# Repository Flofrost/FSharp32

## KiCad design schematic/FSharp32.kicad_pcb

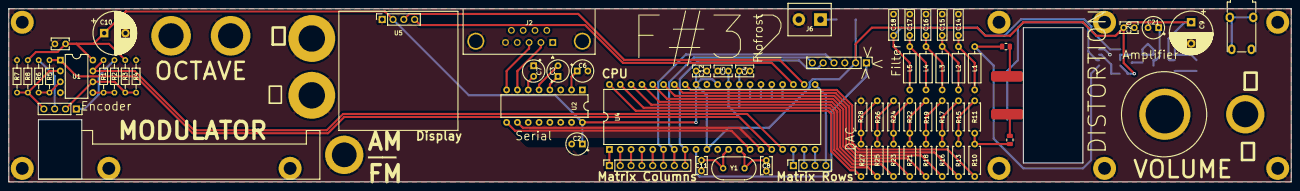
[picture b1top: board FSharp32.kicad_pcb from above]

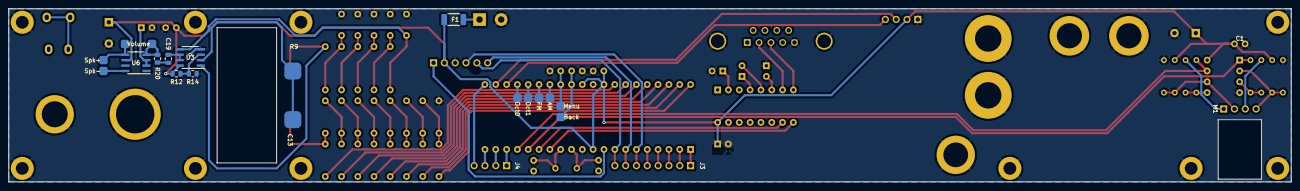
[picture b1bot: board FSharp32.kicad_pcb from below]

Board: 2 copper layers, 301.0 x 40.6 mm, 69 parts (7 on the bottom side), 66 nets.

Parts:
C1, C4, C5, C12, C20: 100n; C_Rect_L4.0mm_W2.5mm_P2.50mm
C2, C3, C6, C7, C21: 10u; CP_Radial_Tantal_D5.0mm_P2.50mm
C8, C11: 18p; C_Rect_L4.0mm_W2.5mm_P2.50mm
C9, C10: 100u; CP_Radial_D10.0mm_P5.00mm
C13, C19: C; C_0805_2012Metric
C14, C15, C16, C17, C18: 94p; C_Rect_L7.0mm_W2.0mm_P5.00mm
F1: Fuse; Fuse_2010_5025Metric
J1: PICkit2; PinHeader_1x06_P2.54mm_Vertical
J2: SerialPort; DSUB-9_Male_Horizontal_P2.77x2.84mm_EdgePinOffset4.94mm_Hou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
J3: MatrixCols; PinSocket_1x08_P2.54mm_Vertical
J4: MatrixRows; PinSocket_1x04_P2.54mm_Vertical
J5: AudioJack2_Ground; Jack_3.5mm_Lumberg_1503_07_Horizontal
J6: POWER; TerminalBlock_bornier-2_P5.08mm
L1, L2, L3, L4, L5: 56m; L_Axial_L6.6mm_D2.7mm_P10.16mm_Horizontal_Vishay_IM-2
M1: Stepper; PinSocket_1x04_P2.54mm_Vertical
R1, R5: 680k; R_Axial_DIN0204_L3.6mm_D1.6mm_P7.62mm_Horizontal
R2, R3, R4, R6, R7, R8: 10k; R_Axial_DIN0204_L3.6mm_D1.6mm_P7.62mm_Horizontal
R9, R20: 56k; R_0805_2012Metric
R10, R13, R16, R18, R21, R23, R25, R27, R28: 2k; R_Axial_DIN0207_L6.3mm_D2.5mm_P7.62mm_Horizontal
R11, R15, R17, R19, R22, R24, R26: 1k; R_Axial_DIN0207_L6.3mm_D2.5mm_P7.62mm_Horizontal
R12, R14: R; R_0805_2012Metric
U1: TLC3702; DIP-8_W7.62mm
U2: MAX232; DIP-16_W7.62mm
U3: MCP6002-xSN; SOIC-8_3.9x4.9mm_P1.27mm
U4: ATmega32-16P; DIP-40_W15.24mm
U5: SSD1306; PinSocket_1x04_P2.54mm_Vertical
U6: LM4861; SOIC-8_3.9x4.9mm_P1.27mm
Y1: 16M; Resonator-2Pin_W10.0mm_H5.0mm

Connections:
+5V: C1.1, C2.1, C9.1, C10.1, C12.1, C20.1, F1.1, J1.2, R3.2, R8.2, R12.1, U1.8 (V+), U2.16 (VCC), U3.8 (V+), U4.10 (VCC), U4.30 (AVCC), U4.32 (AREF), U5.2 (VCC), U6.6 (Vcc)
BackBtn: C5.1, U4.29 (PC7)
CLK: J1.5, J3.8, U4.8 (PB7)
DAC0: R27.1, U4.40 (PA0)
DAC1: R25.1, U4.39 (PA1)
DAC2: R23.1, U4.38 (PA2)
DAC3: R21.1, U4.37 (PA3)
DAC4: R18.1, U4.36 (PA4)
DAC5: R16.1, U4.35 (PA5)
DAC6: R13.1, U4.34 (PA6)
DAC7: R10.1, U4.33 (PA7)
GND: C1.2, C2.2, C4.2, C5.2, C6.2, C7.1, C8.1, C9.2, C10.2, C11.1, C12.2, C14.2, C15.2, C16.2, C17.2, C18.2, C20.2, C21.2, J1.3, J2.0 (PAD), J2.5, J6.2, R4.2, R7.2, R14.2, R28.2, U1.4 (V-), U2.15 (GND), U3.4 (V-), U4.11 (GND), U4.31 (GND), U5.1 (GND), U6.7 (GND)
MISO: J1.6, J3.7, U4.7 (PB6)
MOSI: J1.4, J3.6, U4.6 (PB5)
MenuBtn: C4.1, U4.28 (PC6)
unnamed: C13.2, R10.2, R11.1
unnamed: C14.1, L1.2, L2.1
unnamed: C15.1, L2.2, L3.1
unnamed: C16.1, L3.2, L4.1
unnamed: C17.1, L4.2, L5.1
unnamed: C19.1, R20.2
unnamed: J3.1, U4.1 (PB0)
unnamed: J3.2, U4.2 (PB1)
unnamed: J3.3, U4.3 (PB2)
unnamed: J3.4, U4.4 (PB3)
unnamed: J3.5, U4.5 (PB4)
unnamed: F1.2, J6.1
unnamed: L1.1, R9.2, U3.1
unnamed: M1.2 (-), R3.1, R4.1, U1.6 (-)
unnamed: M1.1, R2.2
unnamed: M1.3, R6.2
unnamed: R11.2, R13.2, R15.1
unnamed: R15.2, R16.2, R17.1
unnamed: R17.2, R18.2, R19.1
unnamed: R19.2, R21.2, R22.1
unnamed: R22.2, R23.2, R24.1
unnamed: R24.2, R25.2, R26.1
unnamed: R26.2, R27.2, R28.1
unnamed: J5.S, J5.T
unnamed: R5.2, R6.1, U1.3 (+)
unnamed: M1.4, R7.1, R8.1, U1.2 (-)
unnamed: R1.2, R2.1, U1.5 (+)
unnamed: C3.1, U2.4 (C2+)
unnamed: C3.2, U2.5 (C2-)
unnamed: J2.3, U2.8 (R2IN)
unnamed: J2.2, U2.7 (T2OUT)
unnamed: C6.1, U2.2 (VS+)
unnamed: C7.2, U2.6 (VS-)
unnamed: R12.2, R14.1, U3.3 (+)
unnamed: C18.1, L5.2, U3.5 (+)
unnamed: C19.2, U3.6 (-), U3.7
unnamed: C8.2, U4.13 (XTAL1), Y1.1
unnamed: C11.2, U4.12 (XTAL2), Y1.2
unnamed: C21.1, U6.2 (BP), U6.3 (+)
unnamed: R20.1, U6.4 (-)
PhaseA: R5.1, U1.1, U4.16 (PD2)
PhaseB: R1.1, U1.7, U4.17 (PD3)
RESET: J1.1, U4.9 (~RESET)
Row0: J4.1, U4.18 (PD4)
Row1: J4.2, U4.19 (PD5)
Row2: J4.3, U4.20 (PD6)
Row3: J4.4, U4.21 (PD7)
Rx: U2.9 (R2OUT), U4.14 (PD0)
SCL: U4.22 (PC0), U5.3 (SCL)
SDA: U4.23 (PC1), U5.4 (SDA)
Tx: U2.10 (T2IN), U4.15 (PD1)

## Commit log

2023-04-09 begun schematic
2023-04-09 continued schematic
2023-04-10 continued schematic (finished rotary encoder)
2023-04-12 made sine function
2023-04-14 progress on schematic
2023-04-17 progress schematic
2023-04-18 schematic progress
2023-04-19 schematic finalized (next footprints)
2023-04-21 begun pcb
2023-04-21 pcb progress
2023-04-22 continued pcb
2023-04-23 finished routing
2023-04-23 finished PCB
2023-04-23 fully finished pcb and order placed
2023-05-07 started drive for ssd1306
2023-05-07 ssd1306 works!!!
2023-05-07 testing printChar
2023-05-07 tweaked printChar function
2023-05-07 Finished font
2023-05-07 fixed printStr
2023-05-11 did some vribrato
2023-05-12 vibrato working!!
2023-05-12 *screeching*
2023-05-12 added octave support and tremolo
2023-05-13 keyboard gaming
2023-05-13 it kinda works?
2023-05-13 fixed a little bit, still issues with frequencies
2023-05-15 supports 4 voices
2023-05-16 more things :)
2023-05-17 text yes
2023-05-17 main screen progress
2023-05-18 more menu support
2023-05-18 instruments support
2023-05-18 stash merge
2023-05-18 can change instruments :)
2023-05-18 menu for envelope
2023-05-19 enveloppe management successful
2023-05-19 enveloppe manu wip
2023-05-20 added guitar + sample extractor
2023-05-20 finished envelope menu (?) + transposed key board to noarrow the range and skip only 1 pctave
2023-05-20 updated font + save file for font
2023-05-21 revamped main screen, profiles wip
2023-05-27 can load profiles
2023-05-28 keyboard complete?!
2023-05-28 added Noise
2023-05-28 added new instruments
2023-05-29 back on main screen resets voices
2023-05-29 added ins + icons
2023-05-30 fixed display bug
2023-05-30 can now upload samples through serial port, hooray
2023-06-02 updated scripts, fixed bug, improved voice reset button
2023-06-04 imporved voice allocator
2023-06-04 fixed bug (again for real this time)
